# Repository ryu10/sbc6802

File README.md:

# SBC6802 plus Bus

[Ja](READMEj.md) | En

Rev. 2

An MC6802-based single board computer. The board design is derived from SBC6800 and SBC6809.

## Features

* MC6802 1MHz
* RAM 32KB (0x0000 - 0x7fff)
* ROM 16KB (0xc000 - 0xffff x two banks, selectable using JP1)
* ACIA (0x8018/0x8019)
* SBC-Bus 2.0 Connector

## In This Repository

The following files are included, along with the KiCAD project:

* [Schematic](sbc6802_r2_sch.pdf)
* [Gerber](sbc6802_gerber_r2.zip)
* [BOM](sbc6802_r2_BOM.pdf)

## Programming PIC12F1822

PIC12F1822（U7）can be programmed with ```osc1536.hex``` found in [SBC6800 datapack](http://www.amy.hi-ho.ne.jp/officetetsu/storage/sbc6800_datapack.zip) to generate the clock for 6850 ACIA. The serial port will operate at 9600 bps.
## SBC-Bus

The bus connector J1 supports [SBC-Bus 2.0](https://store.shopping.yahoo.co.jp/orangepicoshop/pico-a-008.html). Pin 38 is routed to 6802 VMA.

If the board is not connected to the SBC-Bus, connect the 5V and GND pins to a +5V regulated power supply.

## Software

Most of the 6800 software found in [SBC6800 datapack](http://www.amy.hi-ho.ne.jp/officetetsu/storage/sbc6800_datapack.zip) are compatible with SBC6802.

## References

* [SBC6800](https://www.switch-science.com/catalog/3581/) / [Technical Data PDF](http://www.amy.hi-ho.ne.jp/officetetsu/storage/en/sbc6800_techdata.pdf)
* [SBC6809](https://www.switch-science.com/catalog/3583/)
* [SBC-Bus 2.0](https://store.shopping.yahoo.co.jp/orangepicoshop/pico-a-008.html)
* [as0 Motorola 6800 Assembler](https://github.com/JimInCA/motorola-6800-assembler)
* [M6800 Assembly VSCode Extension](https://marketplace.visualstudio.com/items?itemName=RyuStudio.m6800-as0)

## License

CC-BY-SA 3.0
2019 ryu10/RyuStudio.

Derived from the original works of SBC6800 and SBC6809 (c) 2017-2018 Tetsuya Suzuki.

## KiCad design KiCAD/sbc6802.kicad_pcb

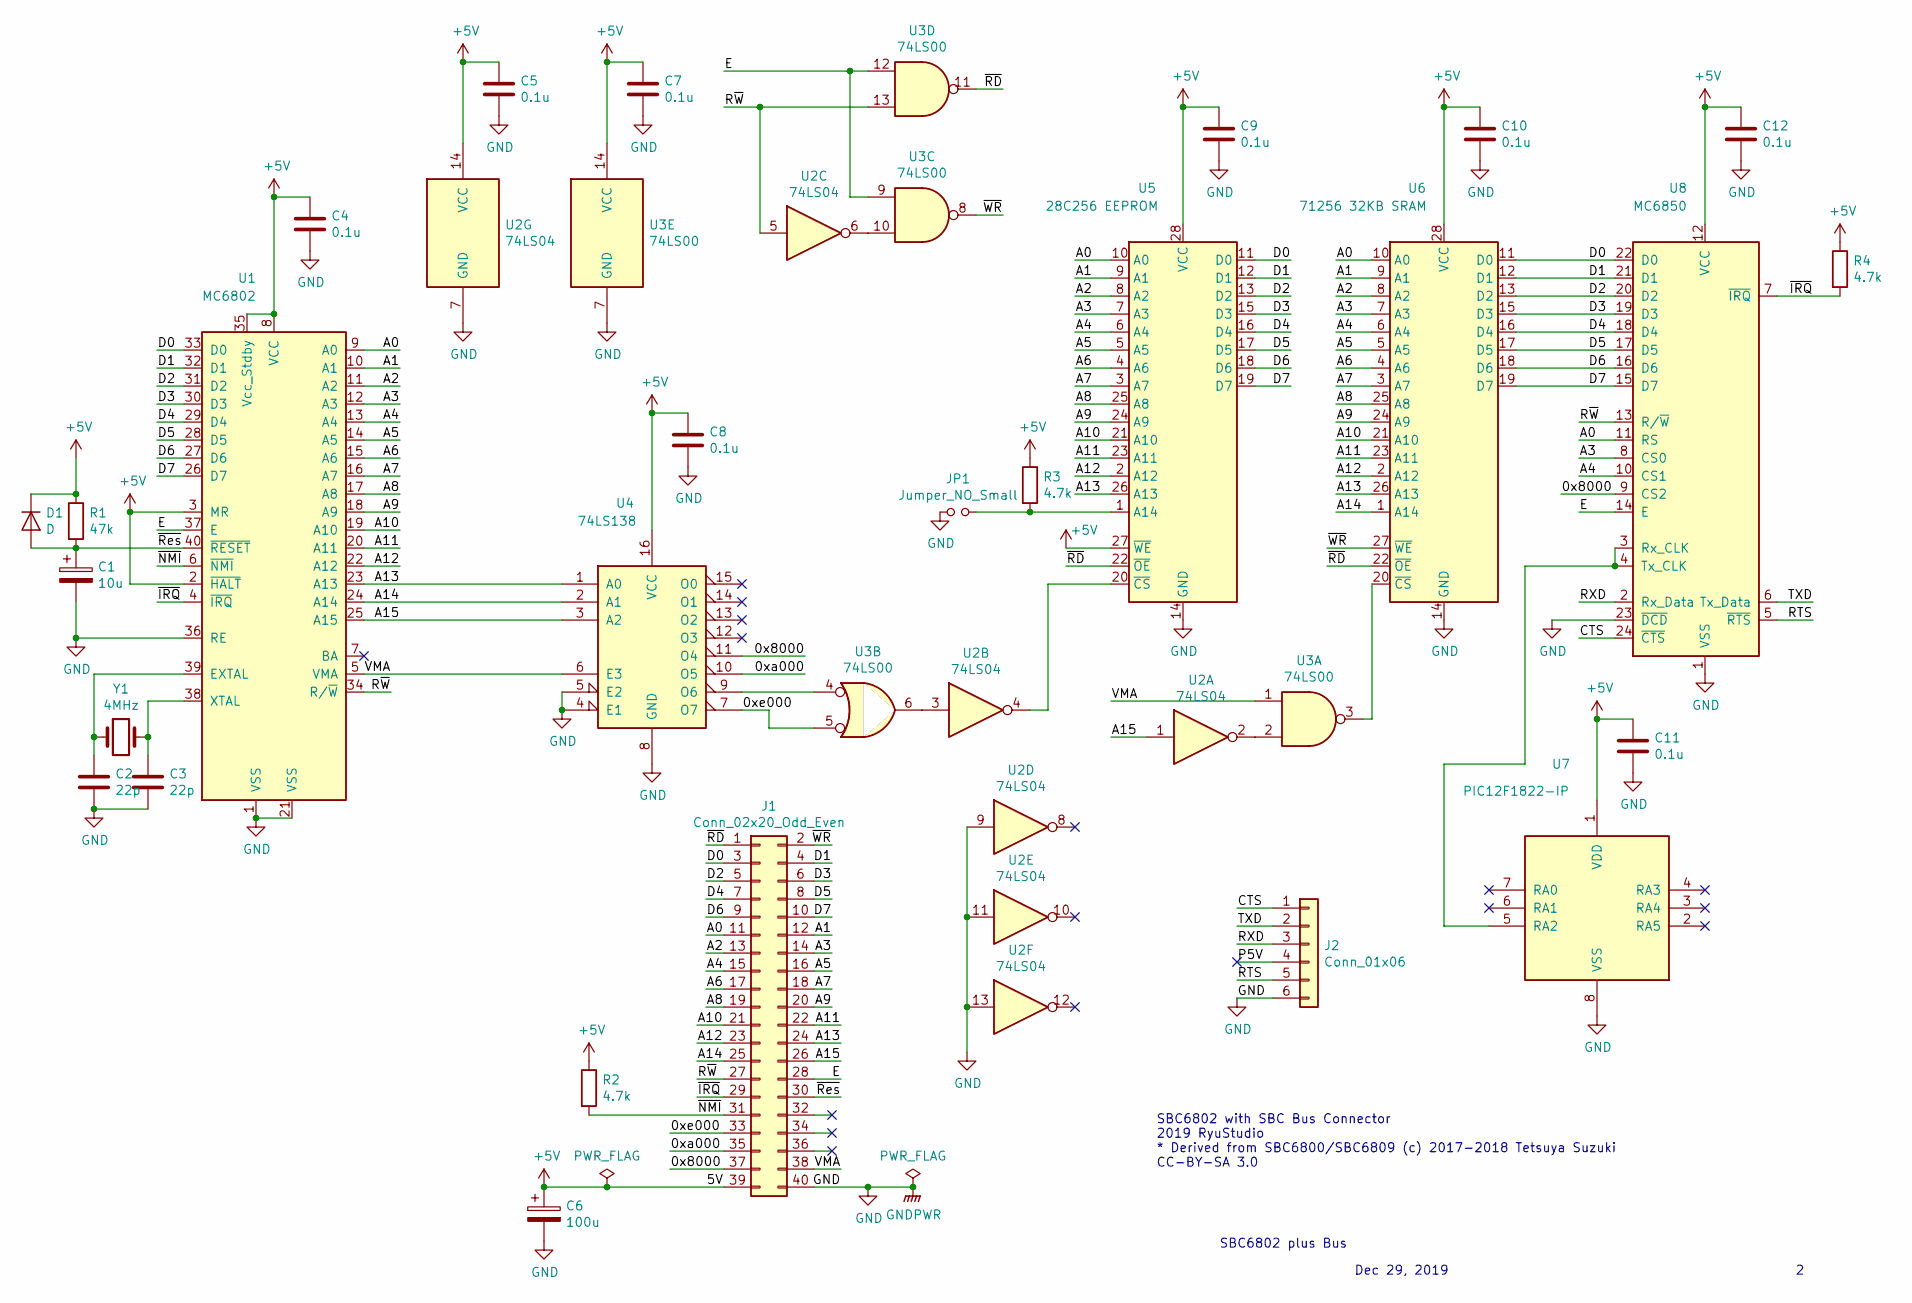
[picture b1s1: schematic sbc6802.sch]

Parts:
C1: 10u; CP_Radial_Tantal_D4.5mm_P2.50mm
C2, C3: 22p; C_Disc_D3.8mm_W2.6mm_P2.50mm
C4, C5, C7, C8, C9, C10, C11, C12: 0.1u; C_Disc_D3.8mm_W2.6mm_P2.50mm
C6: 100u; CP_Radial_Tantal_D4.5mm_P2.50mm
D1: D; D_A-405_P7.62mm_Horizontal
J1: Conn_02x20_Odd_Even; PinHeader_2x20_P2.54mm_Vertical
J2: Conn_01x06; PinHeader_1x06_P2.54mm_Vertical
JP1: Jumper_NO_Small; PinHeader_1x02_P2.54mm_Vertical
R1: 47k; R_Axial_DIN0207_L6.3mm_D2.5mm_P7.62mm_Horizontal
R2, R3, R4: 4.7k; R_Axial_DIN0207_L6.3mm_D2.5mm_P7.62mm_Horizontal
U1: MC6802; DIP-40_W15.24mm
U2: 74LS04; DIP-14_W7.62mm
U3: 74LS00; DIP-14_W7.62mm
U4: 74LS138; DIP-16_W7.62mm
U5: 28C256 EEPROM; DIP-28_W15.24mm
U6: 71256 32KB SRAM; DIP-28_W7.62mm
U7: PIC12F1822-IP; DIP-8_W7.62mm
U8: MC6850; DIP-24_W15.24mm
Y1: 4MHz; R_Axial_DIN0204_L3.6mm_D1.6mm_P5.08mm_Horizontal

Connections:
+5V: C4.1, C5.1, C6.1, C7.1, C8.1, C9.1, C10.1, C11.1, C12.1, D1.1 (K), J1.39, R1.1, R2.1, R3.1, R4.1, U1.2 (~HALT), U1.3 (MR), U1.8 (VCC), U1.35 (Vcc_Stdby), U2.14 (VCC), U3.14 (VCC), U4.16 (VCC), U5.27 (~WE), U5.28 (VCC), U6.28 (VCC), U7.1 (VDD), U8.12 (VCC)
/0x8000: J1.37, U4.11 (O4), U8.9 (CS2)
/0xa000: J1.35, U4.10 (O5)
/0xe000: J1.33, U3.5, U4.7 (O7)
/A0: J1.11, U1.9 (A0), U5.10 (A0), U6.10 (A0), U8.11 (RS)
/A1: J1.12, U1.10 (A1), U5.9 (A1), U6.9 (A1)
/A2: J1.13, U1.11 (A2), U5.8 (A2), U6.8 (A2)
/A3: J1.14, U1.12 (A3), U5.7 (A3), U6.7 (A3), U8.8 (CS0)
/A4: J1.15, U1.13 (A4), U5.6 (A4), U6.6 (A4), U8.10 (CS1)
/A5: J1.16, U1.14 (A5), U5.5 (A5), U6.5 (A5)
/A6: J1.17, U1.15 (A6), U5.4 (A6), U6.4 (A6)
/A7: J1.18, U1.16 (A7), U5.3 (A7), U6.3 (A7)
/A8: J1.19, U1.17 (A8), U5.25 (A8), U6.25 (A8)
/A9: J1.20, U1.18 (A9), U5.24 (A9), U6.24 (A9)
/A10: J1.21, U1.19 (A10), U5.21 (A10), U6.21 (A10)
/A11: J1.22, U1.20 (A11), U5.23 (A11), U6.23 (A11)
/A12: J1.23, U1.22 (A12), U5.2 (A12), U6.2 (A12)
/A13: J1.24, U1.23 (A13), U4.1 (A0), U5.26 (A13), U6.26 (A13)
/A14: J1.25, U1.24 (A14), U4.2 (A1), U6.1 (A14)
/A15: J1.26, U1.25 (A15), U2.1, U4.3 (A2)
/CTS: J2.1, U8.24 (~CTS)
/D0: J1.3, U1.33 (D0), U5.11 (D0), U6.11 (D0), U8.22 (D0)
/D1: J1.4, U1.32 (D1), U5.12 (D1), U6.12 (D1), U8.21 (D1)
/D2: J1.5, U1.31 (D2), U5.13 (D2), U6.13 (D2), U8.20 (D2)
/D3: J1.6, U1.30 (D3), U5.15 (D3), U6.15 (D3), U8.19 (D3)
/D4: J1.7, U1.29 (D4), U5.16 (D4), U6.16 (D4), U8.18 (D4)
/D5: J1.8, U1.28 (D5), U5.17 (D5), U6.17 (D5), U8.17 (D5)
/D6: J1.9, U1.27 (D6), U5.18 (D6), U6.18 (D6), U8.16 (D6)
/D7: J1.10, U1.26 (D7), U5.19 (D7), U6.19 (D7), U8.15 (D7)
/E: J1.28, U1.37 (E), U3.9, U3.12, U8.14 (E)
/RTS: J2.5, U8.5 (~RTS)
/RXD: J2.3, U8.2 (Rx_Data)
/R~W: J1.27, U1.34 (R/~W), U2.5, U3.13, U8.13 (R/~W)
/TXD: J2.2, U8.6 (Tx_Data)
/VMA: J1.38, U1.5 (VMA), U3.1, U4.6 (E3)
/~IRQ: J1.29, R4.2, U1.4 (~IRQ), U8.7 (~IRQ)
/~NMI: J1.31, R2.2, U1.6 (~NMI)
/~RD: J1.1, U3.11, U5.22 (~OE), U6.22 (~OE)
/~Res: C1.1, D1.2 (A), J1.30, R1.2, U1.40 (~RESET)
/~WR: J1.2, U3.8, U6.27 (~WE)
GND: C1.2, C2.2, C3.2, C4.2, C5.2, C6.2, C7.2, C8.2, C9.2, C10.2, C11.2, C12.2, J1.40, J2.6, JP1.1, U1.1 (VSS), U1.21 (VSS), U1.36 (RE), U2.7 (GND), U2.9, U2.11, U2.13, U3.7 (GND), U4.4 (E1), U4.5 (E2), U4.8 (GND), U5.14 (GND), U6.14 (GND), U7.8 (VSS), U8.1 (VSS), U8.23 (~DCD)
unnamed: C2.1, U1.39 (EXTAL), Y1.1
unnamed: C3.1, U1.38 (XTAL), Y1.2
unnamed: JP1.2, R3.2, U5.1 (A14)
unnamed: U2.2, U3.2
unnamed: U2.3, U3.6
unnamed: U2.4, U5.20 (~CS)
unnamed: U2.6, U3.10
unnamed: U3.3, U6.20 (~CS)
unnamed: U3.4, U4.9 (O6)
unnamed: U7.5 (RA2), U8.3 (Rx_CLK), U8.4 (Tx_CLK)

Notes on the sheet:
SBC6802 plus Bus
Dec 29, 2019
SBC6802 with SBC Bus Connector 2019 RyuStudio * Derived from SBC6800/SBC6809 (c) 2017-2018 Tetsuya Suzuki CC-BY-SA 3.0

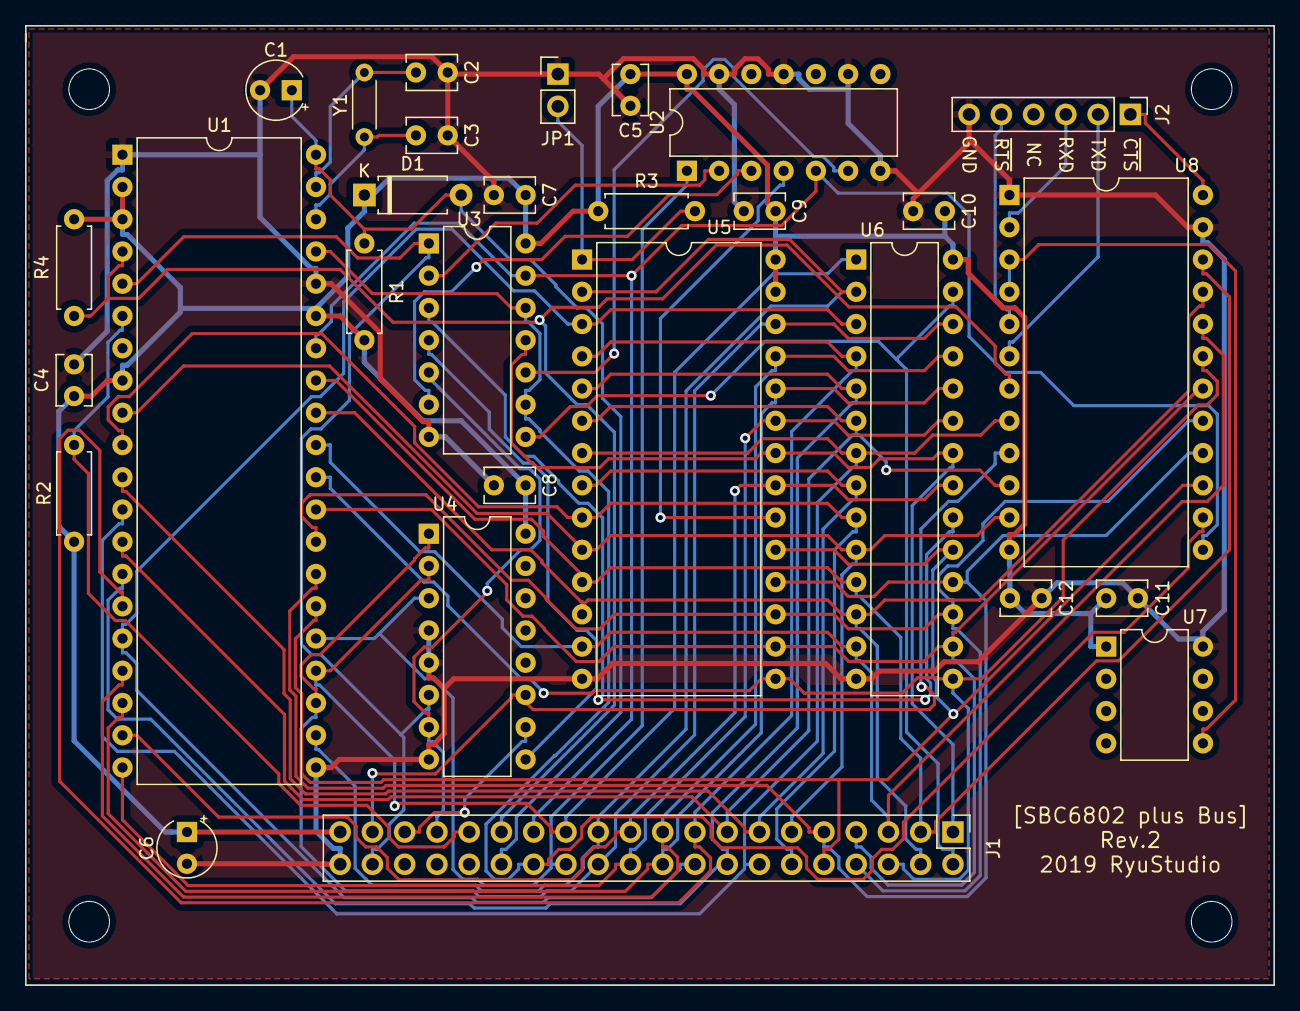
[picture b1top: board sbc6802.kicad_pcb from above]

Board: 2 copper layers, 98.3 x 75.6 mm, 34 parts (1 on the bottom side), 51 nets.

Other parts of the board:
logo1: LOGO; qr_github_sbc6802_r2
mh1, mh2, mh3, mh4: M3; MountingHole_3.2mm_M3

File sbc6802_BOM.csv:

"Id";"Designator";"Package";"Quantity";"Designation";"Supplier and ref";
1;"J2";"PinHeader_1x06_P2.54mm_Horizontal";1;"Conn_01x06";;;
2;"G1";"qr_github_sbc6802";1;"LOGO";;;
3;"D1";"D_DO-35_SOD27_P7.62mm_Horizontal";1;"DIODE";;;
4;"MH2,MH4,MH3,MH1";"MountingHole_3.2mm_M3";4;"MountingHole_3.2mm_M3";;;
5;"C1";"CP_Radial_Tantal_D4.5mm_P2.50mm";1;"10u";;;
6;"C2,C3";"C_Disc_D3.8mm_W2.6mm_P2.50mm";2;"22p";;;
7;"JP1";"PinHeader_1x02_P2.54mm_Vertical";1;"Jumper_NO_Small";;;
8;"R1";"R_Axial_DIN0207_L6.3mm_D2.5mm_P7.62mm_Horizontal";1;"47k";;;
9;"R2,R3,R4";"R_Axial_DIN0207_L6.3mm_D2.5mm_P7.62mm_Horizontal";3;"4.7k";;;
10;"J1";"PinHeader_2x20_P2.54mm_Vertical";1;"Conn_02x20_Odd_Even";;;
11;"U1";"DIP-40_W15.24mm";1;"MC6802";;;
12;"U2";"DIP-14_W7.62mm";1;"74LS04";;;
13;"U3";"DIP-14_W7.62mm";1;"74LS00";;;
14;"U4";"DIP-16_W7.62mm";1;"74LS138";;;
15;"U5";"DIP-28_W15.24mm";1;"28C256 EEPROM";;;
16;"U6";"DIP-28_W7.62mm";1;"71256 32KB SRAM";;;
17;"U7";"DIP-8_W7.62mm";1;"PIC12F1822-IP";;;
18;"U8";"DIP-24_W15.24mm";1;"MC6850";;;
19;"Y1";"R_Axial_DIN0204_L3.6mm_D1.6mm_P5.08mm_Horizontal";1;"4MHz";;;
20;"C11,C10,C12,C4,C5,C7,C8,C9";"C_Disc_D3.8mm_W2.6mm_P2.50mm";8;"0.1u";;;
21;"C6";"CP_Radial_Tantal_D4.5mm_P2.50mm";1;"100u";;;
22;",,";"";3;"";;;

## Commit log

2019-11-16 initial
2019-11-16 readme
2019-11-20 gerber
2019-11-20 schematics
2019-11-22 eesch
2019-11-30 kicad dir
2019-11-30 move graphics dir
2019-12-02 init rev2
2019-12-03 rev2 pcb & readme
2019-12-30 rev2 kicad/gerber
2019-12-31 rev2 gerber
2019-12-31 rev2 readme
2021-02-19 Update Readmes
